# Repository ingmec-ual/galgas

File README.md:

# galgas
Esquemas y firmware de sistemas de medición de tensiones con galgas

Contenido de los directorios: 

  * `galgas-didacticas`: Esquemas en formato Eagle CAD y PDF.
  * `galgas_firmware`: Firmware con proyecto AtmelStudio, usando librería C++ de Arduino IDE. El programa principal es [Sketch.cpp](https://github.com/ingmec-ual/galgas/blob/master/galgas_firmware/galgas_firmware/firmware/Sketch.cpp).

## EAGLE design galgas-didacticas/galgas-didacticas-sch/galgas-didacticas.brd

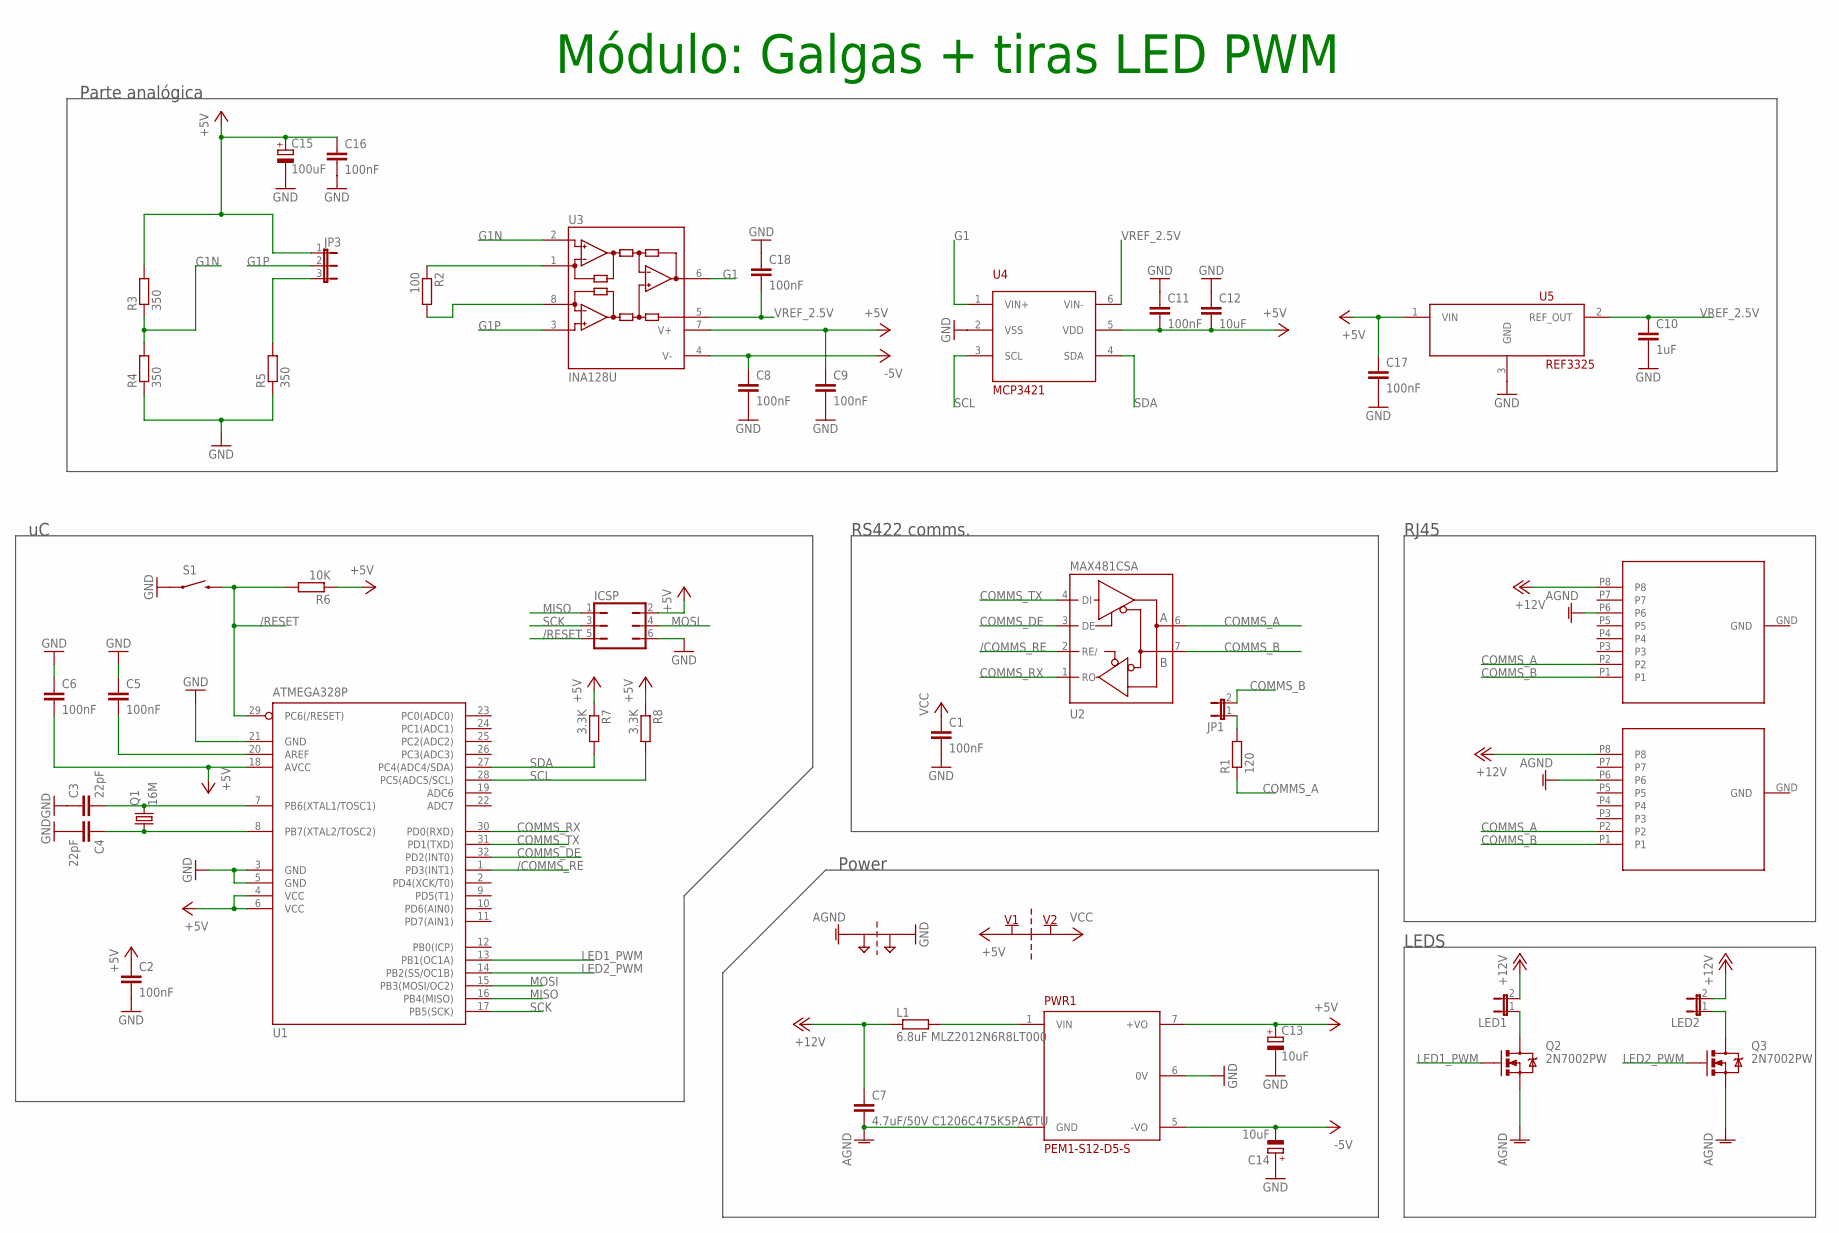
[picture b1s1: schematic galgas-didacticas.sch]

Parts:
C1, C2, C5, C6, C8, C9, C11, C16, C17, C18: 100nF; C0805
C3, C4: 22pF; C0805
C7: 4.7uF/50V C1206C475K5PACTU; C1206K
C10: 1uF; C0805
C12: 10uF; C0805
C13, C14: 10uF; 153CLV-0505
C15: 100uF; 153CLV-0505
ICSP: JP3Q
J1, J2: RJ45_DIRECT
JP1: JP1E; JP1
JP3: JP2E; JP2
L1: 6.8uF MLZ2012N6R8LT000; R0805W
LED1, LED2: JP1E; JP1
PT1: 2PT_GND_TIE
PWR1: PEM1-S12-D5-S; PEM1-S
Q1: 16M; HC49UP
Q2, Q3: 2N7002PW; SOT323
R1: 120; R0805W
R2: 100; R0805W
R3, R4, R5: 350; R1206W
R6: 10K; R0805W
R7, R8: 3.3K; R0805W
S1: SWITCH-MOMENTARY-2PTH; TACTILE-PTH
U1: ATMEGA328P; TQFP32-08
U2: MAX481CSA; SO08
U3: INA128U; SO08
U4: MCP3421; SOT-23-6
U5: REF3325; SOT-23
U$2: SUPPLY_CONNECT; 2PT_GND_TIE

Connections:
+5V: C2.1, C6.2, C9.1, C11.2, C12.2, C13.+, C15.+, C16.1, C17.1, ICSP.2, JP3.1, PWR1.7 (+VO), R3.2, R6.1, R7.1, R8.1, U1.4 (VCC), U1.6 (VCC), U1.18 (AVCC), U3.7 (V+), U4.5 (VDD), U5.1 (VIN), U$2.P$1
+12V: C7.1, J1.P8, J2.P8, L1.1, LED1.2, LED2.2
-5V: C8.1, C14.-, PWR1.5 (-VO), U3.4 (V-)
/COMMS_RE: U1.1 (PD3(INT1)), U2.2 (RE/)
/RESET: ICSP.5, R6.2, S1.3 (2), U1.29 (PC6(/RESET))
AGND: C7.2, J1.P6, J2.P6, PT1.P$1, PWR1.2 (GND), Q2.2 (S), Q3.2 (S)
COMMS_A: J1.P2, J2.P2, R1.1, U2.6 (A)
COMMS_B: J1.P1, J2.P1, JP1.2, U2.7 (B)
COMMS_DE: U1.32 (PD2(INT0)), U2.3 (DE)
COMMS_RX: U1.30 (PD0(RXD)), U2.1 (RO)
COMMS_TX: U1.31 (PD1(TXD)), U2.4 (DI)
G1: U3.6 (OUT), U4.1 (VIN+)
G1N: R3.1, R4.2, U3.2 (-IN)
G1P: JP3.2, U3.3 (+IN)
GND: C1.2, C2.2, C3.1, C4.2, C5.1, C6.1, C8.2, C9.2, C10.2, C11.1, C12.1, C13.-, C14.+, C15.-, C16.2, C17.2, C18.1, ICSP.6, J1.GND, J2.GND, PT1.P$2, PWR1.6 (0V), R4.1, R5.1, S1.1, U1.3 (GND), U1.5 (GND), U1.21 (GND), U2.5 (GND), U4.2 (VSS), U5.3 (GND)
LED1_PWM: Q2.1 (G), U1.13 (PB1(OC1A))
LED2_PWM: Q3.1 (G), U1.14 (PB2(SS/OC1B))
MISO: ICSP.1, U1.16 (PB4(MISO))
MOSI: ICSP.4, U1.15 (PB3(MOSI/OC2))
unnamed: JP1.1, R1.2
unnamed: LED1.1, Q2.3 (D)
unnamed: C3.2, Q1.2, U1.7 (PB6(XTAL1/TOSC1))
unnamed: C4.1, Q1.1, U1.8 (PB7(XTAL2/TOSC2))
unnamed: C5.2, U1.20 (AREF)
unnamed: L1.2, PWR1.1 (VIN)
unnamed: R2.1, U3.1 (RG)
unnamed: R2.2, U3.8 (RG)
unnamed: LED2.1, Q3.3 (D)
unnamed: JP3.3, R5.2
SCK: ICSP.3, U1.17 (PB5(SCK))
SCL: R8.2, U1.28 (PC5(ADC5/SCL)), U4.3 (SCL)
SDA: R7.2, U1.27 (PC4(ADC4/SDA)), U4.4 (SDA)
VCC: C1.1, U2.8 (VCC), U$2.P$2
VREF_2.5V: C10.1, C18.2, U3.5 (REF), U4.6 (VIN-), U5.2 (REF_OUT)

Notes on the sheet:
LEDS
RJ45
RS422 comms.
Power
Parte analógica
Módulo: Galgas + tiras LED PWM

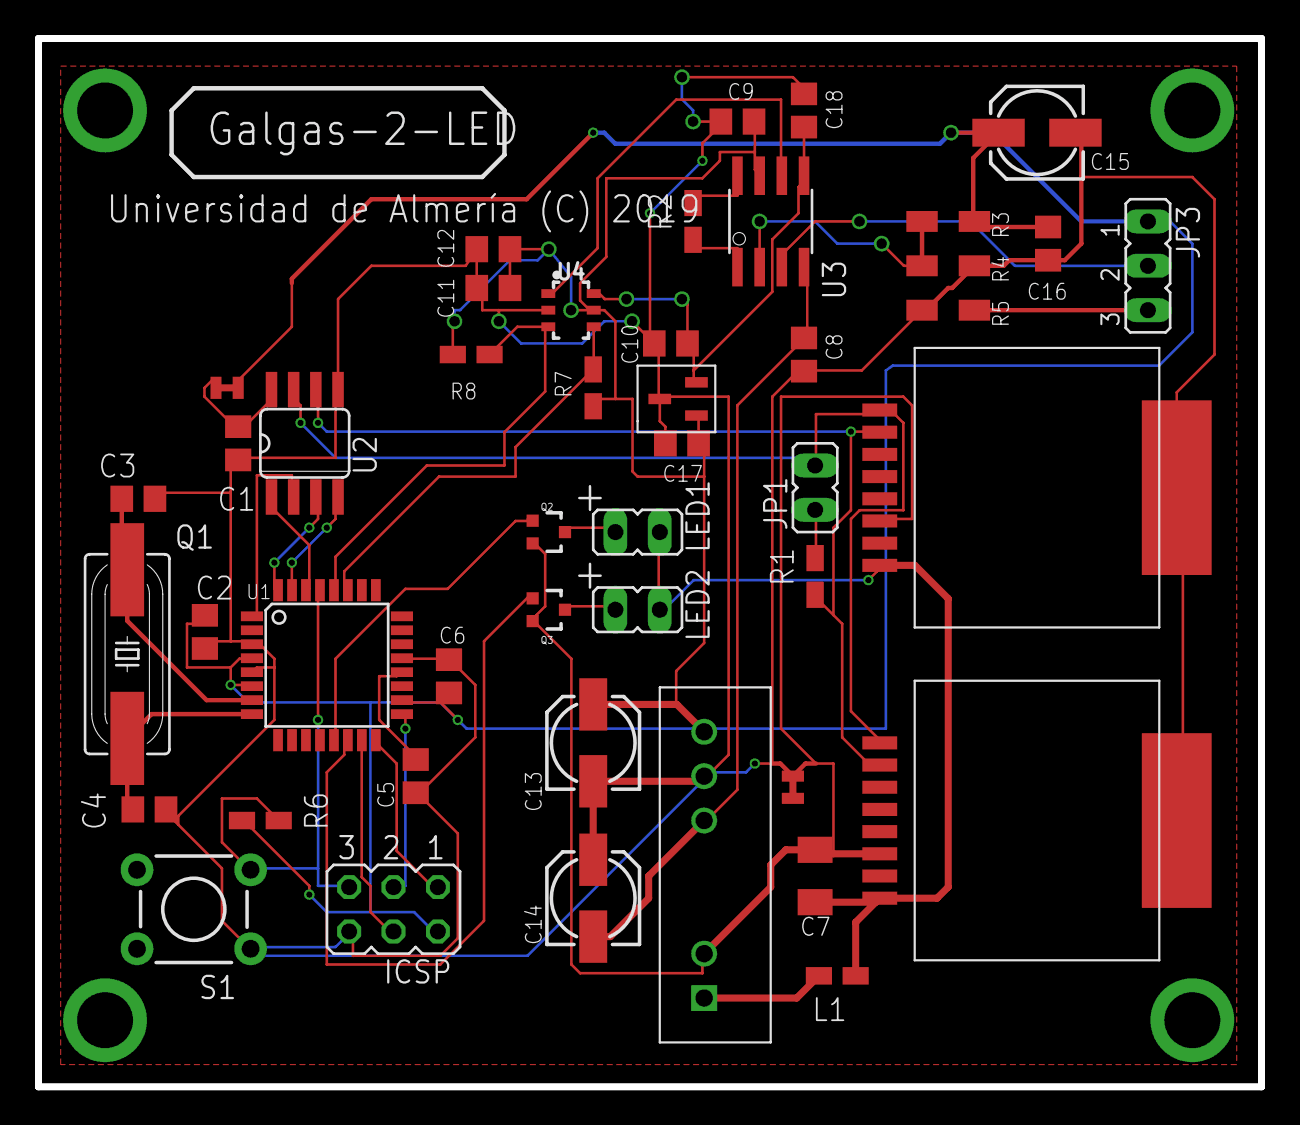
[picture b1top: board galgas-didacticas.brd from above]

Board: 2 copper layers, 70.0 x 60.0 mm, 46 parts (0 on the bottom side), 34 nets.

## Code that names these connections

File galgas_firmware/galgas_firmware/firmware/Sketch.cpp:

/*
  Sketch.cpp - Main file for "Didactic Strain Gauges-LED System"
  Copyright (c) 2018-2019 University of Almeria.  All right reserved.

  This library is free software; you can redistribute it and/or
  modify it under the terms of the GNU Lesser General Public
  License as published by the Free Software Foundation; either
  version 2.1 of the License, or (at your option) any later version.

  This library is distributed in the hope that it will be useful,
  but WITHOUT ANY WARRANTY; without even the implied warranty of
  MERCHANTABILITY or FITNESS FOR A PARTICULAR PURPOSE.  See the GNU
  Lesser General Public License for more details.

  You should have received a copy of the GNU Lesser General Public
  License along with this library; if not, write to the Free Software
  Foundation, Inc., 51 Franklin St, Fifth Floor, Boston, MA  02110-1301  USA
*/

// Firmware designed for ATMEGA328P
// Note: to enable sprintf() of doubles/floats, link with these flags:
// -Wl,-u,vfprintf -lprintf_flt -lm

#include <Arduino.h>
#include <EEPROM.h>
#include <Wire.h>
#include "MCP342X.h"

// Uncomment to enable sending debug text messages to the serial console.
// do NOT leave enabled for production, since several devices would try 
// to write simultaneously to the RS485 bus without arbitration.
//#define SERIAL_DEBUG_MSGS

// LEDs:
constexpr int LED1_PIN = 9; // uC pin 13, PB1
constexpr int LED2_PIN = 10; // uC pin 14, PB2

constexpr int SERIAL_DE_PIN  = 2; // uC pin 32, PD2
constexpr int SERIAL_nRE_PIN = 3; // uC pin 1, PD3

// The ADC:
static MCP342X adc;
static bool adc_init_ok = false;
static const auto ADC_GAIN = MCP342X_GAIN_1X;
static uint8_t MY_ID = 0xff; // My unique board ID, stored in EEPROM

// The residual strain, acquired after reset:
static int16_t adc_zero_strain_offset = 0;

// Last measured strain, in ADC bit units (after offset compensation):
static int32_t measured_real_strain = 0;

// Calculated such as V_adc=0.3 ==> 100% of PWM LED output
static double STRAIN_TO_PWM_CONST = 255.5/ (0.3 * ((2<<15 - 1) / 2.5));

static double threshold_strain_leds = 100;


// func. decls:
static void process_sensors_leds();
static void process_command(const char*cmd);
static void do_led_ramp_up_down(int led_id, int delay_speed_ms = 6);
static void rs485_enable_tx();
static void rs485_enable_rx();
static void rs485_send_string(const char* s);
static uint8_t id_read(); // Read "my ID" from EEPROM
static void id_write(uint8_t id); // write "my ID" to EEPROM


void setup()
{
	// Flash LEDs at start up:
	do_led_ramp_up_down(LED1_PIN, 3);
	do_led_ramp_up_down(LED2_PIN, 3);

	// Init I2C bus:
	Wire.begin();
	// Use max I2C speed (400 kHz)
	TWBR = 12;

	// Read ID from eeprom
	MY_ID = id_read();

	// Configure RS485 control outputs:
	pinMode(SERIAL_DE_PIN, OUTPUT);
	pinMode(SERIAL_nRE_PIN, OUTPUT);
	rs485_enable_rx();

	// Init serial port:
	Serial.begin(115200);

	// read timeout (ms)
	Serial.setTimeout(5);

	// wait for Serial comms to become ready
	while (!Serial) {}
		
}

void loop()
{
	// Test connection to ADC once after boot up:
	// --------------------------------------------------
	if (!adc_init_ok)
	{
#ifdef SERIAL_DEBUG_MSGS
		rs485_send_string("# Testing ADC connection...");
#endif

		adc_init_ok = adc.testConnection();
		if (adc_init_ok)
		{
#ifdef SERIAL_DEBUG_MSGS
			rs485_send_string("# MCP342X connection successful!");
#endif

			adc.configure(
				MCP342X_MODE_CONTINUOUS |
				MCP342X_CHANNEL_1 |
				MCP342X_SIZE_16BIT |
				ADC_GAIN
				);

#ifdef SERIAL_DEBUG_MSGS
			rs485_enable_tx();
			Serial.print("# ADC config register=");
			Serial.println(adc.getConfigRegShdw(), HEX);
			Serial.flush();
			rs485_enable_rx();
#endif

			// Read a few samples (a discard them) waiting for the 
			// analog value to stabilize after reset, then take it as 
			// the "residual strain" offset value:
			// (16bit -> continuous rate of 15 SPS)
			for (int i=0;i<15;i++)
			{
				adc.startConversion();
				adc.getResult(&adc_zero_strain_offset);
			}

#ifdef SERIAL_DEBUG_MSGS
			rs485_enable_tx();
			Serial.print("# Using ADC offset value=");
			Serial.println(adc_zero_strain_offset);
			Serial.flush();
			rs485_enable_rx();
#endif
		}
		else
		{
#ifdef SERIAL_DEBUG_MSGS
			rs485_send_string("# MCP342X connection failed! Retrying in 1 second...");
#endif
			delay(1000);
			return;
		}
	}
	

	// Main ADC reading task:
	process_sensors_leds();

	// check for commands from the PC:
	String sCmd = Serial.readStringUntil('\n');
	if (sCmd.length()>2)
	{
		process_command(sCmd.c_str());
	}
}

// Main task: read ADC and flash LEDs accordingly
void process_sensors_leds()
{
	int16_t  adc_value;
	adc.startConversion();
	adc.getResult(&adc_value);
	
	// Strain is measured - offset (residual structural strain)
	measured_real_strain = adc_value - adc_zero_strain_offset;
	
	// Convert to PWM (0-255)
	double pwm_value_f= .0;
	if (fabs(measured_real_strain)>threshold_strain_leds)
	{
		pwm_value_f = STRAIN_TO_PWM_CONST * measured_real_strain;
	}

	// Saturate:
	const bool is_negative = (pwm_value_f<0);
	if (pwm_value_f<0) pwm_value_f=-pwm_value_f;
	if (pwm_value_f>255) pwm_value_f = 255;
	uint8_t pwm_value = static_cast<uint8_t>(pwm_value_f);
	
	// TODO: positive / negative, one LED or the other one.
	analogWrite(is_negative ? LED2_PIN : LED1_PIN, pwm_value);
	analogWrite(is_negative ? LED1_PIN : LED2_PIN, 0);
}


void do_led_ramp_up_down(int led_id, int delay_speed_ms)
{
	pinMode(led_id, OUTPUT);

	for (int pc = 0; pc <255; pc++)
	{
		analogWrite(led_id, pc);
		delay(delay_speed_ms);
	}
	for (int pc = 255; pc >0; pc--)
	{
		analogWrite(led_id, pc);
		delay(delay_speed_ms);
	}

}

void rs485_enable_tx()
{
	digitalWrite(SERIAL_DE_PIN, true);
	digitalWrite(SERIAL_nRE_PIN, true);
}

void rs485_enable_rx()
{
	digitalWrite(SERIAL_DE_PIN, false);
	digitalWrite(SERIAL_nRE_PIN, false);
}

void rs485_send_string(const char* s)
{
	rs485_enable_tx();
	Serial.print("TX:");
	Serial.println(s);
	Serial.flush();
	rs485_enable_rx();
}

// Read "my ID" from EEPROM
uint8_t id_read()
{
	return EEPROM.read(0x00);
}

// write "my ID" to EEPROM
void id_write(uint8_t id)
{
	EEPROM.write(0x00,id);
}

// Forward declaration of command functions:
static void do_cmd_id();
static void do_cmd_get(const char* varname);
static void do_cmd_set(const char* varname, double value);
static void do_cmd_setid(uint8_t new_id);

// Checks whether "str" starts with "substr"
static inline bool startsWith(const char* str, const char* substr)
{
	return !strncasecmp(str,substr, strlen(substr));
}

/* Format of commands:
*
* TO <ID> <CMD> <ARGS...>
*
*/
void process_command(const char*cmd)
{
	// Windows may be slow to reset the RTS signal so the hardware RS485 board parses our sent data, 
	// so make sure of inserting a "large" delay before we transmit anything:
	delay(30); // ms

	const auto len = strlen(cmd);
	if (len<3)
	{
		// wrong command? corrupt data?
		return;
	}

	if (!startsWith(cmd,"TO "))
	{
		rs485_send_string("does not start TO\n");
		return;
	}

	int target_id = 0xEE; // init to invalid value
	if (!sscanf(cmd+3,"%i",&target_id))
	{
		// Couldn't parse. Don't answer with an error code since we were not sure 
		// about whether the message was sent to this board (!).
		return;
	}

	if (target_id!=MY_ID)
	{
		// silently ignore this commands: it's not for us.
		return;
	}

	// advance cmd pointer to the next useful position:
	cmd+=3;
	while (*cmd!=' ')
	{
		if (*cmd=='\0') return;
		++cmd;
	}
	// Start with the next non blank char:
	cmd++;

	if (!strncmp(cmd,"ID",2))
	{
		return do_cmd_id();
	}
	if (!strncmp(cmd,"SETID ",6))
	{
		unsigned int new_id=0;
		if (1==sscanf(cmd+6,"%u",&new_id))
		{
			do_cmd_setid(new_id);
			return rs485_send_string("OK|ID changed.\n");
		}
		else
		{
			return rs485_send_string("ERROR|Cannot parse new ID value\n");
		}
	}
	if (!strncmp(cmd,"GET ",4))
	{
		return do_cmd_get(cmd+4);
	}

	char s[60];
	sprintf(s,"ERROR|Unrecognized command: `%.20s`\n", cmd);
	rs485_send_string(s);
}

void do_cmd_id()
{
	char s[60];
	sprintf(s,"OK|GalgasDidactivas ID=%u Build: " __TIMESTAMP__  "\n", id_read());
	rs485_send_string(s);
}


void do_cmd_setid(uint8_t new_id)
{
	id_write(new_id);
	MY_ID = new_id;
}

void do_cmd_get(const char* varname)
{
	char s[60];
	if (startsWith(varname,"STRAIN"))
	{
		sprintf(s,"OK|%i\n", measured_real_strain);
		return rs485_send_string(s);
	}
	if (startsWith(varname,"OFFSET"))
	{
		sprintf(s,"OK|%i\n", adc_zero_strain_offset);
		return rs485_send_string(s);
	}
	if (startsWith(varname,"PWM_CONST"))
	{
		sprintf(s,"OK|%u\n", static_cast<unsigned int>(STRAIN_TO_PWM_CONST*1000U));
		return rs485_send_string(s);
	}

	rs485_send_string("ERROR|GET: Unrecognized variable name\n");
}

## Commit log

2018-09-26 1st sch
2018-10-18 add components lib
2018-10-23 Progress
2018-10-31 add PEM1-S12-D5-S
2018-11-06 Add EuroCircuits DRU
2018-11-06 First "final" version of the SCH
2018-11-08 Board routing done
2018-11-08 mejoras (más condensadores desacoplo, etc.)
2018-11-12 planos GND
2018-12-27 Import Arduino firmware to Atmel Studio
2018-12-27 led ramp function
2019-01-09 Import MCP342X library
2019-01-09 read ADC and flash LEDs accordingly
2019-01-10 minor fix
2019-01-10 fix saturate
2019-01-17 Explicación de contenido directorios
2019-01-17 Actualizo constante
2019-10-09 importar a git primera version
2019-10-09 crear matriz casos
2019-10-11 Reescribo script posicion
2019-10-11 añado script matriz constante
2019-10-11 modifico script posicion
2019-10-14 elimino script antiguos
2019-10-14 modifico imagines para que tengan el mismo tamaño
2019-10-14 modifico ortografía de los comentarios de los script
2019-10-14 creo la interfaz del programa
2019-10-14 modificacion interfaz
2019-10-15 creo gráfica del puente
2019-10-15 puente cambia de color al estar sometido a compresion
2019-10-15 añado a la interfaz puente que cambia de color T/C
2019-10-15 solucion problema superposicion colores T/C
2019-10-16 simplifico calculo peso
2019-10-16 añado y modifico comentarios
2019-10-16 elimino archivos temporales
2019-10-16 modifico y añado comentarios explicativos
2019-10-22 añado comentarios de licencia
2019-10-23 primer intento de añadir temporizador
2019-10-23 solucionar fallo
2019-10-23 Solucion temporizador
2019-10-25 Corrijo errores ortograficos
2019-11-11 correciones varias
2019-11-11 popupmenu comienza al pulsar boton medir
2019-11-18 cambio cg global a handles
2019-11-18 Activo y desactivo boton medir
2019-11-22 Primera version clase de comunicaciones puerto serie
2019-11-22 progreso comunicaciones
2019-11-23 Implement rs485 comms protocol
2020-01-20 progress debugging serial comms
2020-01-21 comms delays fixed
2020-02-03 actualizaciones
2020-02-03 corrección del peso y nombre de las barras sensorizadas
2020-02-04 añadir cuadro dialogo preguntando por el puerto serie
2020-02-05 DIALOGO PUERTO SERIE
2020-02-05 start new measure API
2020-02-05 Añadir botones conectar/desconectar
2020-02-05 LEDs: histeresis y apagar correctamente
2020-02-05 Progress with ADCs readings
2020-02-05 calculo de la epsilon a partir del voltaje
2020-02-10 Primer intento de checkbox
2020-02-13 segunda prueba de checkbox
2020-02-21 Solución checkbox definitiva
2020-03-11 ajuste al tamaño pantalla
2020-03-11 solucionar boton desconectar
2020-03-11 tabla todas las filas a la vez
2020-04-15 primer intento boton simulacion/real
2020-04-22 Segundo intento de boton simulacion/real
2020-04-22 soluciono problemas de unidades
2020-05-24 Nombrar las barras seleccionadas en las imagenes para que concuerden con la tabla
2020-05-24 cambio de tipo de medicion a tipo de resultados
2020-05-24 cambios en traccion y compresion para que salgan todas las barras

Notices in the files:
galgas-didacticas/galgas-didacticas-sch/galgas-didacticas.brd:
Universidad de Almería (C) 2019
parts and their libraries:
SparkFun-Electromechanical: Licensing: Creative Commons ShareAlike 4.0 International - https://creativecommons.org/licenses/by-sa/4.0
